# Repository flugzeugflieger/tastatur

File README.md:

for info the cherry key libraries are from https://github.com/sszczep/Cherry-MX-Breakout-Board

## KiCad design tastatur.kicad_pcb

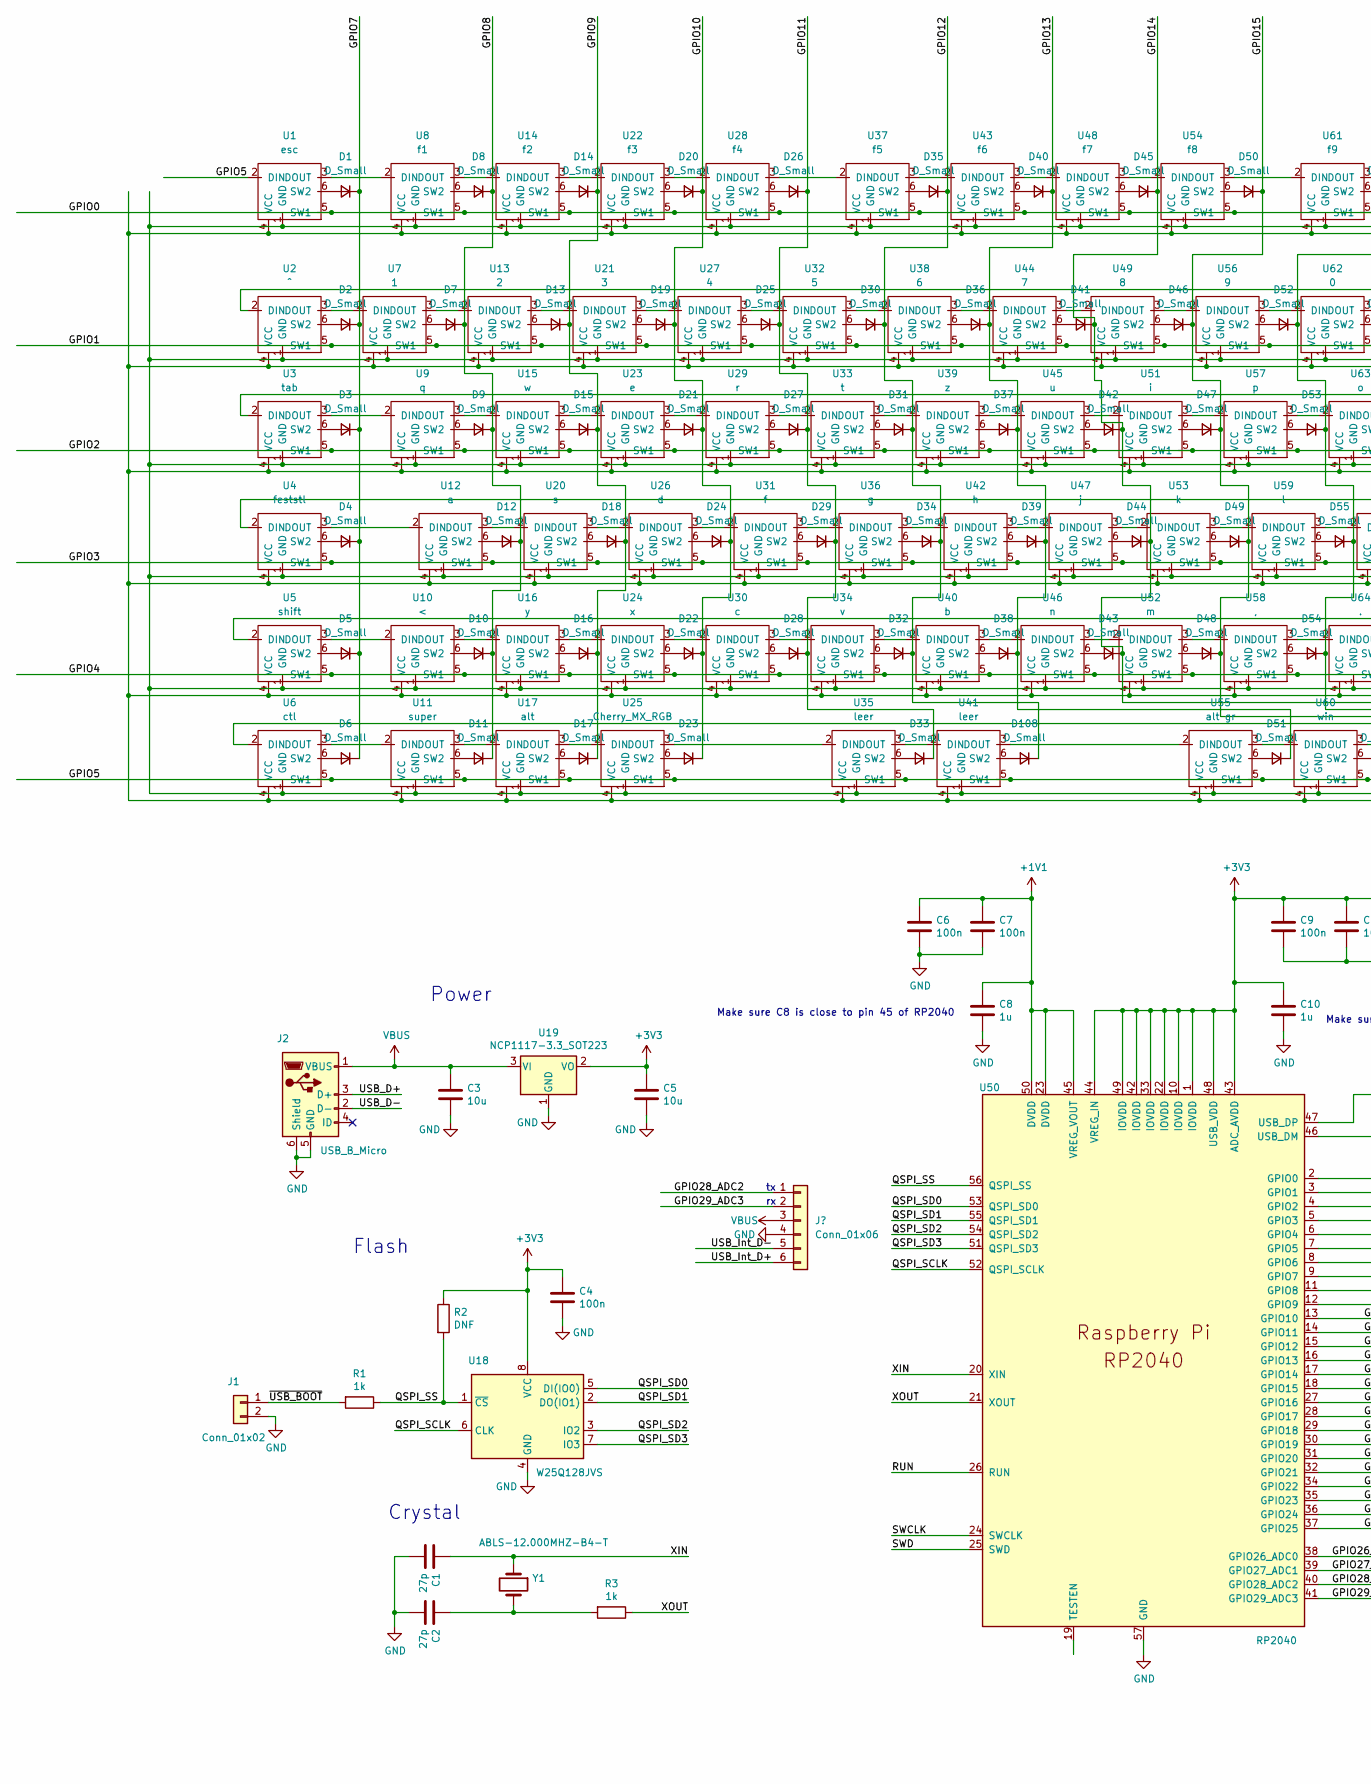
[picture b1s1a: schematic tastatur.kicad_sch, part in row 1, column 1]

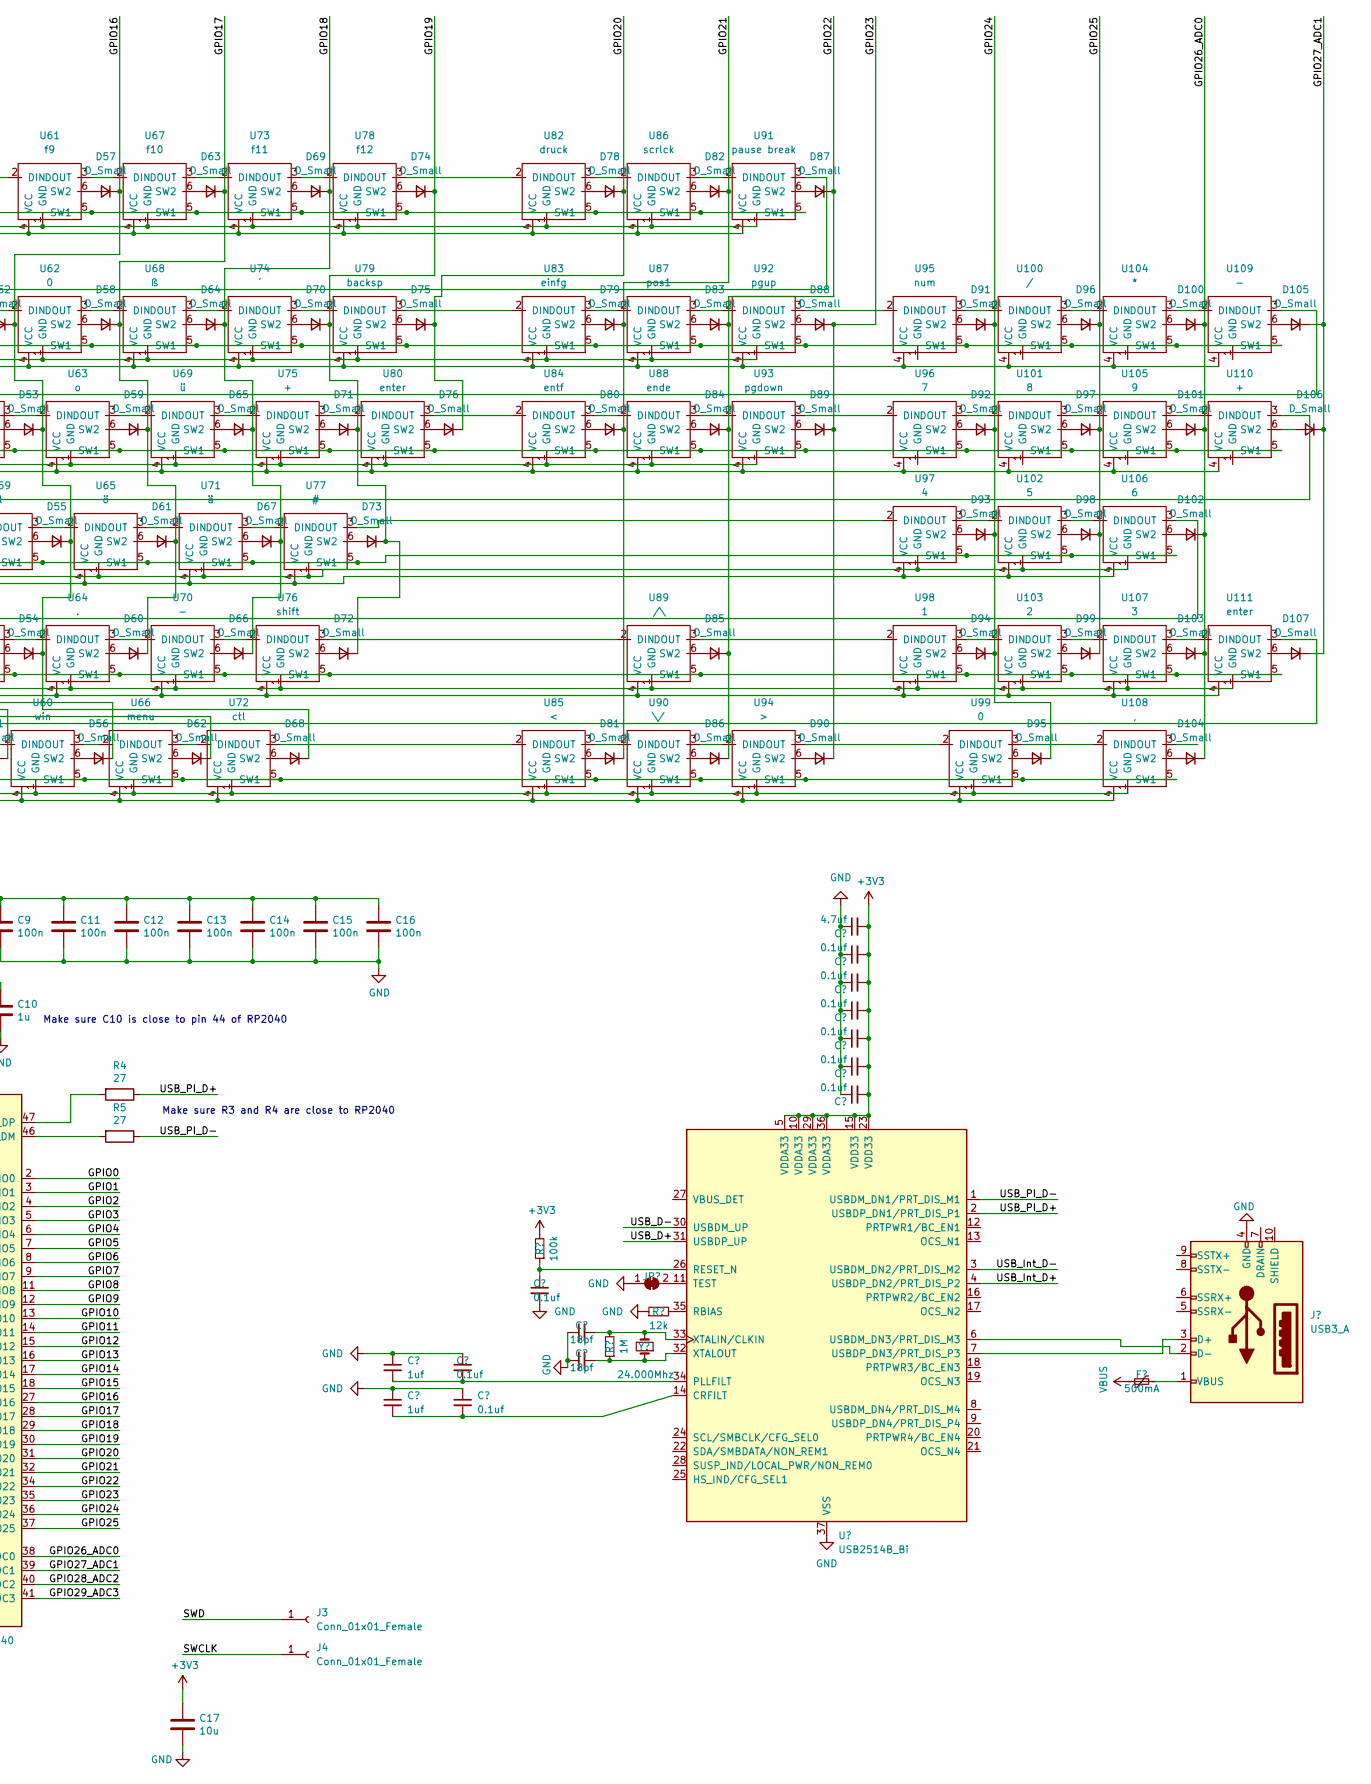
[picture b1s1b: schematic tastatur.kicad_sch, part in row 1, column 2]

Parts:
C1, C2: 27p; C_0402_1005Metric
C3, C5, C17: 10u; C_0805_2012Metric
C4, C6, C7, C9, C11, C12, C13, C14, C15, C16: 100n; C_0402_1005Metric
C8, C10: 1u; C_0402_1005Metric
D1, D2, D3, D4, D5, D6, D7, D8, D9, D10, D11, D12, D13, D14, D15, D16, D17, D18, D19, D20, D21, D22, D23, D24, D25, D26, D27, D28, D29, D30, D31, D32, D33, D34, D35, D36, D37, D38, D39, D40, D41, D42, D43, D44, D45, D46, D47, D48, D49, D50, D51, D52, D53, D54, D55, D56, D57, D58, D59, D60, D61, D62, D63, D64, D65, D66, D67, D68, D69, D70, D71, D72, D73, D74, D75, D76, D78, D79, D80, D81, D82, D83, D84, D85, D86, D87, D88, D89, D90, D91, D92, D93, D94, D95, D96, D97, D98, D99, D100, D101, D102, D103, D104, D105, D106, D107, D108: D_Small; D_SMA
J1: Conn_01x02; PinHeader_1x02_P2.54mm_Vertical
J2: USB_B_Micro; USB_Micro-B_Amphenol_10103594-0001LF_Horizontal_modified
J3: Conn_01x01_Female; LED-L1T2_LUMILEDS
J4: Conn_01x01_Female; PinSocket_1x01_P2.54mm_Vertical
R1, R3: 1k; C_0402_1005Metric
R2: DNF; C_0402_1005Metric
R4, R5: 27; C_0402_1005Metric
U1: esc; Cherry-MX_PCB-Mounted_LTST-A683CEGBW_Mill-Max-7305
U2: ^; Cherry-MX_PCB-Mounted_LTST-A683CEGBW_Mill-Max-7305
U3: tab; Cherry-MX_PCB-Mounted_LTST-A683CEGBW_Mill-Max-7305
U4: feststl; Cherry-MX_PCB-Mounted_LTST-A683CEGBW_Mill-Max-7305
U5, U76: shift; Cherry-MX_PCB-Mounted_LTST-A683CEGBW_Mill-Max-7305
U6, U72: ctl; Cherry-MX_PCB-Mounted_LTST-A683CEGBW_Mill-Max-7305
U7, U98: 1; Cherry-MX_PCB-Mounted_LTST-A683CEGBW_Mill-Max-7305
U8: f1; Cherry-MX_PCB-Mounted_LTST-A683CEGBW_Mill-Max-7305
U9: q; Cherry-MX_PCB-Mounted_LTST-A683CEGBW_Mill-Max-7305
U10, U85: <; Cherry-MX_PCB-Mounted_LTST-A683CEGBW_Mill-Max-7305
U11: super; Cherry-MX_PCB-Mounted_LTST-A683CEGBW_Mill-Max-7305
U12: a; Cherry-MX_PCB-Mounted_LTST-A683CEGBW_Mill-Max-7305
U13, U103: 2; Cherry-MX_PCB-Mounted_LTST-A683CEGBW_Mill-Max-7305
U14: f2; Cherry-MX_PCB-Mounted_LTST-A683CEGBW_Mill-Max-7305
U15: w; Cherry-MX_PCB-Mounted_LTST-A683CEGBW_Mill-Max-7305
U16: y; Cherry-MX_PCB-Mounted_LTST-A683CEGBW_Mill-Max-7305
U17: alt; Cherry-MX_PCB-Mounted_LTST-A683CEGBW_Mill-Max-7305
U18: W25Q128JVS; SOIC-8_5.23x5.23mm_P1.27mm
U19: NCP1117-3.3_SOT223; SOT-223-3_TabPin2
U20: s; Cherry-MX_PCB-Mounted_LTST-A683CEGBW_Mill-Max-7305
U21, U107: 3; Cherry-MX_PCB-Mounted_LTST-A683CEGBW_Mill-Max-7305
U22: f3; Cherry-MX_PCB-Mounted_LTST-A683CEGBW_Mill-Max-7305
U23: e; Cherry-MX_PCB-Mounted_LTST-A683CEGBW_Mill-Max-7305
U24: x; Cherry-MX_PCB-Mounted_LTST-A683CEGBW_Mill-Max-7305
U25: Cherry_MX_RGB; Cherry-MX_PCB-Mounted_LTST-A683CEGBW_Mill-Max-7305
U26: d; Cherry-MX_PCB-Mounted_LTST-A683CEGBW_Mill-Max-7305
U27, U97: 4; Cherry-MX_PCB-Mounted_LTST-A683CEGBW_Mill-Max-7305
U28: f4; Cherry-MX_PCB-Mounted_LTST-A683CEGBW_Mill-Max-7305
U29: r; Cherry-MX_PCB-Mounted_LTST-A683CEGBW_Mill-Max-7305
U30: c; Cherry-MX_PCB-Mounted_LTST-A683CEGBW_Mill-Max-7305
U31: f; Cherry-MX_PCB-Mounted_LTST-A683CEGBW_Mill-Max-7305
U32, U102: 5; Cherry-MX_PCB-Mounted_LTST-A683CEGBW_Mill-Max-7305
U33: t; Cherry-MX_PCB-Mounted_LTST-A683CEGBW_Mill-Max-7305
U34: v; Cherry-MX_PCB-Mounted_LTST-A683CEGBW_Mill-Max-7305
U35, U41: leer; Cherry-MX_PCB-Mounted_LTST-A683CEGBW_Mill-Max-7305
U36: g; Cherry-MX_PCB-Mounted_LTST-A683CEGBW_Mill-Max-7305
U37: f5; Cherry-MX_PCB-Mounted_LTST-A683CEGBW_Mill-Max-7305
U38, U106: 6; Cherry-MX_PCB-Mounted_LTST-A683CEGBW_Mill-Max-7305
U39: z; Cherry-MX_PCB-Mounted_LTST-A683CEGBW_Mill-Max-7305
U40: b; Cherry-MX_PCB-Mounted_LTST-A683CEGBW_Mill-Max-7305
U42: h; Cherry-MX_PCB-Mounted_LTST-A683CEGBW_Mill-Max-7305
U43: f6; Cherry-MX_PCB-Mounted_LTST-A683CEGBW_Mill-Max-7305
U44, U96: 7; Cherry-MX_PCB-Mounted_LTST-A683CEGBW_Mill-Max-7305
U45: u; Cherry-MX_PCB-Mounted_LTST-A683CEGBW_Mill-Max-7305
U46: n; Cherry-MX_PCB-Mounted_LTST-A683CEGBW_Mill-Max-7305
U47: j; Cherry-MX_PCB-Mounted_LTST-A683CEGBW_Mill-Max-7305
U48: f7; Cherry-MX_PCB-Mounted_LTST-A683CEGBW_Mill-Max-7305
U49, U101: 8; Cherry-MX_PCB-Mounted_LTST-A683CEGBW_Mill-Max-7305
U50: RP2040; RP2040-QFN-56
U51: i; Cherry-MX_PCB-Mounted_LTST-A683CEGBW_Mill-Max-7305
U52: m; Cherry-MX_PCB-Mounted_LTST-A683CEGBW_Mill-Max-7305
U53: k; Cherry-MX_PCB-Mounted_LTST-A683CEGBW_Mill-Max-7305
U54: f8; Cherry-MX_PCB-Mounted_LTST-A683CEGBW_Mill-Max-7305
U55: alt gr; Cherry-MX_PCB-Mounted_LTST-A683CEGBW_Mill-Max-7305
U56, U105: 9; Cherry-MX_PCB-Mounted_LTST-A683CEGBW_Mill-Max-7305
U57: p; Cherry-MX_PCB-Mounted_LTST-A683CEGBW_Mill-Max-7305
U58, U108: ,; Cherry-MX_PCB-Mounted_LTST-A683CEGBW_Mill-Max-7305
U59: l; Cherry-MX_PCB-Mounted_LTST-A683CEGBW_Mill-Max-7305
U60: win; Cherry-MX_PCB-Mounted_LTST-A683CEGBW_Mill-Max-7305
U61: f9; Cherry-MX_PCB-Mounted_LTST-A683CEGBW_Mill-Max-7305
U62, U99: 0; Cherry-MX_PCB-Mounted_LTST-A683CEGBW_Mill-Max-7305
U63: o; Cherry-MX_PCB-Mounted_LTST-A683CEGBW_Mill-Max-7305
U64: .; Cherry-MX_PCB-Mounted_LTST-A683CEGBW_Mill-Max-7305
U65: ö; Cherry-MX_PCB-Mounted_LTST-A683CEGBW_Mill-Max-7305
U66: menu; Cherry-MX_PCB-Mounted_LTST-A683CEGBW_Mill-Max-7305
U67: f10; Cherry-MX_PCB-Mounted_LTST-A683CEGBW_Mill-Max-7305
U68: ß; Cherry-MX_PCB-Mounted_LTST-A683CEGBW_Mill-Max-7305
U69: ü; Cherry-MX_PCB-Mounted_LTST-A683CEGBW_Mill-Max-7305
U70, U109: -; Cherry-MX_PCB-Mounted_LTST-A683CEGBW_Mill-Max-7305
U71: ä; Cherry-MX_PCB-Mounted_LTST-A683CEGBW_Mill-Max-7305
U73: f11; Cherry-MX_PCB-Mounted_LTST-A683CEGBW_Mill-Max-7305
U74: ´; Cherry-MX_PCB-Mounted_LTST-A683CEGBW_Mill-Max-7305
U75, U110: +; Cherry-MX_PCB-Mounted_LTST-A683CEGBW_Mill-Max-7305
U77: #; Cherry-MX_PCB-Mounted_LTST-A683CEGBW_Mill-Max-7305
U78: f12; Cherry-MX_PCB-Mounted_LTST-A683CEGBW_Mill-Max-7305
U79: backsp; Cherry-MX_PCB-Mounted_LTST-A683CEGBW_Mill-Max-7305
U80, U111: enter; Cherry-MX_PCB-Mounted_LTST-A683CEGBW_Mill-Max-7305
U82: druck; Cherry-MX_PCB-Mounted_LTST-A683CEGBW_Mill-Max-7305
U83: einfg; Cherry-MX_PCB-Mounted_LTST-A683CEGBW_Mill-Max-7305
U84: entf; Cherry-MX_PCB-Mounted_LTST-A683CEGBW_Mill-Max-7305
U86: scrlck; Cherry-MX_PCB-Mounted_LTST-A683CEGBW_Mill-Max-7305
U87: pos1; Cherry-MX_PCB-Mounted_LTST-A683CEGBW_Mill-Max-7305
U88: ende; Cherry-MX_PCB-Mounted_LTST-A683CEGBW_Mill-Max-7305
U89: /\; Cherry-MX_PCB-Mounted_LTST-A683CEGBW_Mill-Max-7305
U90: \/; Cherry-MX_PCB-Mounted_LTST-A683CEGBW_Mill-Max-7305
U91: pause break; Cherry-MX_PCB-Mounted_LTST-A683CEGBW_Mill-Max-7305
U92: pgup; Cherry-MX_PCB-Mounted_LTST-A683CEGBW_Mill-Max-7305
U93: pgdown; Cherry-MX_PCB-Mounted_LTST-A683CEGBW_Mill-Max-7305
U94: >; Cherry-MX_PCB-Mounted_LTST-A683CEGBW_Mill-Max-7305
U95: num; Cherry-MX_PCB-Mounted_LTST-A683CEGBW_Mill-Max-7305
U100: /; Cherry-MX_PCB-Mounted_LTST-A683CEGBW_Mill-Max-7305
U104: *; Cherry-MX_PCB-Mounted_LTST-A683CEGBW_Mill-Max-7305
Y1: ABLS-12.000MHZ-B4-T; Crystal_SMD_HC49-US

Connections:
+1V1: C6.1, C7.1, C8.1, U50.23 (DVDD), U50.45 (VREG_VOUT), U50.50 (DVDD)
+3V3: C4.1, C5.1, C9.1, C10.1, C11.1, C12.1, C13.1, C14.1, C15.1, C16.1, C17.1, R2.1, U18.8 (VCC), U19.2 (VO), U50.1 (IOVDD), U50.10 (IOVDD), U50.22 (IOVDD), U50.33 (IOVDD), U50.42 (IOVDD), U50.43 (ADC_AVDD), U50.44 (VREG_IN), U50.48 (USB_VDD), U50.49 (IOVDD)
/GPIO0: U1.5 (SW1), U8.5 (SW1), U14.5 (SW1), U22.5 (SW1), U28.5 (SW1), U37.5 (SW1), U43.5 (SW1), U48.5 (SW1), U50.2 (GPIO0), U54.5 (SW1), U61.5 (SW1), U67.5 (SW1), U73.5 (SW1), U78.5 (SW1), U82.5 (SW1), U86.5 (SW1), U91.5 (SW1)
/GPIO1: U2.5 (SW1), U7.5 (SW1), U13.5 (SW1), U21.5 (SW1), U27.5 (SW1), U32.5 (SW1), U38.5 (SW1), U44.5 (SW1), U49.5 (SW1), U50.3 (GPIO1), U56.5 (SW1), U62.5 (SW1), U68.5 (SW1), U74.5 (SW1), U79.5 (SW1), U83.5 (SW1), U87.5 (SW1), U92.5 (SW1), U95.5 (SW1), U100.5 (SW1), U104.5 (SW1), U109.5 (SW1)
/GPIO2: U3.5 (SW1), U9.5 (SW1), U15.5 (SW1), U23.5 (SW1), U29.5 (SW1), U33.5 (SW1), U39.5 (SW1), U45.5 (SW1), U50.4 (GPIO2), U51.5 (SW1), U57.5 (SW1), U63.5 (SW1), U69.5 (SW1), U75.5 (SW1), U80.5 (SW1), U84.5 (SW1), U88.5 (SW1), U93.5 (SW1), U96.5 (SW1), U101.5 (SW1), U105.5 (SW1), U110.5 (SW1)
/GPIO3: U4.5 (SW1), U12.5 (SW1), U20.5 (SW1), U26.5 (SW1), U31.5 (SW1), U36.5 (SW1), U42.5 (SW1), U47.5 (SW1), U50.5 (GPIO3), U53.5 (SW1), U59.5 (SW1), U65.5 (SW1), U71.5 (SW1), U77.5 (SW1), U97.5 (SW1), U102.5 (SW1), U106.5 (SW1)
/GPIO4: U5.5 (SW1), U10.5 (SW1), U16.5 (SW1), U24.5 (SW1), U30.5 (SW1), U34.5 (SW1), U40.5 (SW1), U46.5 (SW1), U50.6 (GPIO4), U52.5 (SW1), U58.5 (SW1), U64.5 (SW1), U70.5 (SW1), U76.5 (SW1), U89.5 (SW1), U98.5 (SW1), U103.5 (SW1), U107.5 (SW1), U111.5 (SW1)
/GPIO5: U1.2 (DIN), U6.5 (SW1), U11.5 (SW1), U17.5 (SW1), U25.5 (SW1), U35.5 (SW1), U41.5 (SW1), U50.7 (GPIO5), U55.5 (SW1), U60.5 (SW1), U66.5 (SW1), U72.5 (SW1), U85.5 (SW1), U90.5 (SW1), U94.5 (SW1), U99.5 (SW1), U108.5 (SW1)
/GPIO7: D1.1 (K), D2.1 (K), D3.1 (K), D4.1 (K), D5.1 (K), D6.1 (K), U50.9 (GPIO7)
/GPIO8: D7.1 (K), D8.1 (K), D9.1 (K), D10.1 (K), D11.1 (K), D12.1 (K), U50.11 (GPIO8)
/GPIO9: D13.1 (K), D14.1 (K), D15.1 (K), D16.1 (K), D17.1 (K), D18.1 (K), U50.12 (GPIO9)
/GPIO10: D19.1 (K), D20.1 (K), D21.1 (K), D22.1 (K), D23.1 (K), D24.1 (K), U50.13 (GPIO10)
/GPIO11: D25.1 (K), D26.1 (K), D27.1 (K), D28.1 (K), D29.1 (K), D33.1 (K), U50.14 (GPIO11)
/GPIO12: D30.1 (K), D31.1 (K), D32.1 (K), D34.1 (K), D35.1 (K), D108.1 (K), U50.15 (GPIO12)
/GPIO13: D36.1 (K), D37.1 (K), D38.1 (K), D39.1 (K), D40.1 (K), D51.1 (K), U50.16 (GPIO13)
/GPIO14: D41.1 (K), D42.1 (K), D43.1 (K), D44.1 (K), D45.1 (K), D56.1 (K), U50.17 (GPIO14)
/GPIO15: D46.1 (K), D47.1 (K), D48.1 (K), D49.1 (K), D50.1 (K), D62.1 (K), U50.18 (GPIO15)
/GPIO16: D52.1 (K), D53.1 (K), D54.1 (K), D55.1 (K), D57.1 (K), D68.1 (K), U50.27 (GPIO16)
/GPIO17: D58.1 (K), D59.1 (K), D60.1 (K), D61.1 (K), D63.1 (K), U50.28 (GPIO17)
/GPIO18: D64.1 (K), D65.1 (K), D66.1 (K), D67.1 (K), D69.1 (K), U50.29 (GPIO18)
/GPIO19: D70.1 (K), D71.1 (K), D72.1 (K), D73.1 (K), D74.1 (K), U50.30 (GPIO19)
/GPIO20: D75.1 (K), D76.1 (K), D78.1 (K), U50.31 (GPIO20)
/GPIO21: D79.1 (K), D80.1 (K), D81.1 (K), D82.1 (K), U50.32 (GPIO21)
/GPIO22: D83.1 (K), D84.1 (K), D85.1 (K), D86.1 (K), D87.1 (K), U50.34 (GPIO22)
/GPIO23: D88.1 (K), D89.1 (K), D90.1 (K), U50.35 (GPIO23)
/GPIO24: D91.1 (K), D92.1 (K), D93.1 (K), D94.1 (K), D95.1 (K), U50.36 (GPIO24)
/GPIO25: D96.1 (K), D97.1 (K), D98.1 (K), D99.1 (K), U50.37 (GPIO25)
/GPIO26_ADC0: D100.1 (K), D101.1 (K), D102.1 (K), D103.1 (K), D104.1 (K), U50.38 (GPIO26_ADC0)
/GPIO27_ADC1: D105.1 (K), D106.1 (K), D107.1 (K), U50.39 (GPIO27_ADC1)
/QSPI_SCLK: U18.6 (CLK), U50.52 (QSPI_SCLK)
/QSPI_SD0: U18.5 (DI(IO0)), U50.53 (QSPI_SD0)
/QSPI_SD1: U18.2 (DO(IO1)), U50.55 (QSPI_SD1)
/QSPI_SD2: U18.3 (IO2), U50.54 (QSPI_SD2)
/QSPI_SD3: U18.7 (IO3), U50.51 (QSPI_SD3)
/QSPI_SS: R1.1, R2.2, U18.1 (~CS), U50.56 (QSPI_SS)
/SWCLK: J4.1, U50.24 (SWCLK)
/SWD: J3.1, U50.25 (SWD)
/USB_D+: R4.1
/USB_D-: R5.1
/XIN: C1.1, U50.20 (XIN), Y1.1
/XOUT: R3.1, U50.21 (XOUT)
/~USB_BOOT: J1.1, R1.2
GND: C1.2, C2.2, C3.2, C4.2, C5.2, C6.2, C7.2, C8.2, C9.2, C10.2, C11.2, C12.2, C13.2, C14.2, C15.2, C16.2, C17.2, J1.2, J2.5 (GND), J2.6 (Shield), U18.4 (GND), U19.1 (GND)
unnamed: C2.1, R3.2, Y1.2
unnamed: D1.2 (A), U1.6 (SW2)
unnamed: D2.2 (A), U2.6 (SW2)
unnamed: D3.2 (A), U3.6 (SW2)
unnamed: D4.2 (A), U4.6 (SW2)
unnamed: D5.2 (A), U5.6 (SW2)
unnamed: D6.2 (A), U6.6 (SW2)
unnamed: D7.2 (A), U7.6 (SW2)
unnamed: D8.2 (A), U8.6 (SW2)
unnamed: D9.2 (A), U9.6 (SW2)
unnamed: D10.2 (A), U10.6 (SW2)
unnamed: D11.2 (A), U11.6 (SW2)
unnamed: D12.2 (A), U12.6 (SW2)
unnamed: D13.2 (A), U13.6 (SW2)
unnamed: D14.2 (A), U14.6 (SW2)
unnamed: D15.2 (A), U15.6 (SW2)
unnamed: D16.2 (A), U16.6 (SW2)
unnamed: D17.2 (A), U17.6 (SW2)
unnamed: D18.2 (A), U20.6 (SW2)
unnamed: D19.2 (A), U21.6 (SW2)
unnamed: D20.2 (A), U22.6 (SW2)
unnamed: D21.2 (A), U23.6 (SW2)
unnamed: D22.2 (A), U24.6 (SW2)
unnamed: D23.2 (A), U25.6 (SW2)
unnamed: D24.2 (A), U26.6 (SW2)
unnamed: D25.2 (A), U27.6 (SW2)
unnamed: D26.2 (A), U28.6 (SW2)
unnamed: D27.2 (A), U29.6 (SW2)
unnamed: D28.2 (A), U30.6 (SW2)
unnamed: D29.2 (A), U31.6 (SW2)
unnamed: D30.2 (A), U32.6 (SW2)
unnamed: D31.2 (A), U33.6 (SW2)
unnamed: D32.2 (A), U34.6 (SW2)
unnamed: D33.2 (A), U35.6 (SW2)
unnamed: D34.2 (A), U36.6 (SW2)
unnamed: D35.2 (A), U37.6 (SW2)
unnamed: D36.2 (A), U38.6 (SW2)
unnamed: D37.2 (A), U39.6 (SW2)
unnamed: D38.2 (A), U40.6 (SW2)
unnamed: D39.2 (A), U42.6 (SW2)
unnamed: D40.2 (A), U43.6 (SW2)
unnamed: D41.2 (A), U44.6 (SW2)
unnamed: D42.2 (A), U45.6 (SW2)
unnamed: D43.2 (A), U46.6 (SW2)
unnamed: D44.2 (A), U47.6 (SW2)
unnamed: D45.2 (A), U48.6 (SW2)
unnamed: D46.2 (A), U49.6 (SW2)
unnamed: D47.2 (A), U51.6 (SW2)
unnamed: D48.2 (A), U52.6 (SW2)
unnamed: D49.2 (A), U53.6 (SW2)
unnamed: D50.2 (A), U54.6 (SW2)
unnamed: D51.2 (A), U55.6 (SW2)
unnamed: D52.2 (A), U56.6 (SW2)
unnamed: D53.2 (A), U57.6 (SW2)
unnamed: D54.2 (A), U58.6 (SW2)
unnamed: D55.2 (A), U59.6 (SW2)
unnamed: D56.2 (A), U60.6 (SW2)
unnamed: D57.2 (A), U61.6 (SW2)
unnamed: D58.2 (A), U62.6 (SW2)
unnamed: D59.2 (A), U63.6 (SW2)
unnamed: D60.2 (A), U64.6 (SW2)
unnamed: D61.2 (A), U65.6 (SW2)
unnamed: D62.2 (A), U66.6 (SW2)
unnamed: D63.2 (A), U67.6 (SW2)
unnamed: D64.2 (A), U68.6 (SW2)
unnamed: D65.2 (A), U69.6 (SW2)
unnamed: D66.2 (A), U70.6 (SW2)
unnamed: D67.2 (A), U71.6 (SW2)
unnamed: D68.2 (A), U72.6 (SW2)
unnamed: D69.2 (A), U73.6 (SW2)
unnamed: D70.2 (A), U74.6 (SW2)
unnamed: D71.2 (A), U75.6 (SW2)
unnamed: D72.2 (A), U76.6 (SW2)
unnamed: D73.2 (A), U77.6 (SW2)
unnamed: D74.2 (A), U78.6 (SW2)
unnamed: D75.2 (A), U79.6 (SW2)
unnamed: D76.2 (A), U80.6 (SW2)
unnamed: D78.2 (A), U82.6 (SW2)
unnamed: D79.2 (A), U83.6 (SW2)
unnamed: D80.2 (A), U84.6 (SW2)
unnamed: D81.2 (A), U85.6 (SW2)
unnamed: D82.2 (A), U86.6 (SW2)
unnamed: D83.2 (A), U87.6 (SW2)
unnamed: D84.2 (A), U88.6 (SW2)
unnamed: D85.2 (A), U89.6 (SW2)
unnamed: D86.2 (A), U90.6 (SW2)
unnamed: D87.2 (A), U91.6 (SW2)
unnamed: D88.2 (A), U92.6 (SW2)
unnamed: D89.2 (A), U93.6 (SW2)
unnamed: D90.2 (A), U94.6 (SW2)
unnamed: D91.2 (A), U95.6 (SW2)
unnamed: D92.2 (A), U96.6 (SW2)
unnamed: D93.2 (A), U97.6 (SW2)
unnamed: D94.2 (A), U98.6 (SW2)
unnamed: D95.2 (A), U99.6 (SW2)
unnamed: D96.2 (A), U100.6 (SW2)
unnamed: D97.2 (A), U101.6 (SW2)
unnamed: D98.2 (A), U102.6 (SW2)
unnamed: D99.2 (A), U103.6 (SW2)
unnamed: D100.2 (A), U104.6 (SW2)
unnamed: D101.2 (A), U105.6 (SW2)
unnamed: D102.2 (A), U106.6 (SW2)
unnamed: D103.2 (A), U107.6 (SW2)
unnamed: D104.2 (A), U108.6 (SW2)
unnamed: D105.2 (A), U109.6 (SW2)
unnamed: D106.2 (A), U110.6 (SW2)
unnamed: D107.2 (A), U111.6 (SW2)
unnamed: R4.2, U50.47 (USB_DP)
unnamed: R5.2, U50.46 (USB_DM)
unnamed: U1.1 (GND), U2.1 (GND), U3.1 (GND), U4.1 (GND), U5.1 (GND), U6.1 (GND), U7.1 (GND), U8.1 (GND), U9.1 (GND), U10.1 (GND), U11.1 (GND), U12.1 (GND), U13.1 (GND), U14.1 (GND), U15.1 (GND), U16.1 (GND), U17.1 (GND), U20.1 (GND), U21.1 (GND), U22.1 (GND), U23.1 (GND), U24.1 (GND), U25.1 (GND), U26.1 (GND), U27.1 (GND), U28.1 (GND), U29.1 (GND), U30.1 (GND), U31.1 (GND), U32.1 (GND), U33.1 (GND), U34.1 (GND), U35.1 (GND), U36.1 (GND), U37.1 (GND), U38.1 (GND), U39.1 (GND), U40.1 (GND), U41.1 (GND), U42.1 (GND), U43.1 (GND), U44.1 (GND), U45.1 (GND), U46.1 (GND), U47.1 (GND), U48.1 (GND), U49.1 (GND), U51.1 (GND), U52.1 (GND), U53.1 (GND), U54.1 (GND), U55.1 (GND), U56.1 (GND), U57.1 (GND), U58.1 (GND), U59.1 (GND), U60.1 (GND), U61.1 (GND), U62.1 (GND), U63.1 (GND), U64.1 (GND), U65.1 (GND), U66.1 (GND), U67.1 (GND), U68.1 (GND), U69.1 (GND), U70.1 (GND), U71.1 (GND), U72.1 (GND), U73.1 (GND), U74.1 (GND), U75.1 (GND), U76.1 (GND), U77.1 (GND), U78.1 (GND), U79.1 (GND), U80.1 (GND), U82.1 (GND), U83.1 (GND), U84.1 (GND), U85.1 (GND), U86.1 (GND), U87.1 (GND), U88.1 (GND), U89.1 (GND), U90.1 (GND), U91.1 (GND), U92.1 (GND), U93.1 (GND), U94.1 (GND), U97.1 (GND), U98.1 (GND), U99.1 (GND), U102.1 (GND), U103.1 (GND), U106.1 (GND), U107.1 (GND), U108.1 (GND), U111.1 (GND)
unnamed: U1.3 (DOUT), U8.2 (DIN)
unnamed: U1.4 (VCC), U2.4 (VCC), U3.4 (VCC), U4.4 (VCC), U5.4 (VCC), U6.4 (VCC), U7.4 (VCC), U8.4 (VCC), U9.4 (VCC), U10.4 (VCC), U11.4 (VCC), U12.4 (VCC), U13.4 (VCC), U14.4 (VCC), U15.4 (VCC), U16.4 (VCC), U17.4 (VCC), U20.4 (VCC), U21.4 (VCC), U22.4 (VCC), U23.4 (VCC), U24.4 (VCC), U25.4 (VCC), U26.4 (VCC), U27.4 (VCC), U28.4 (VCC), U29.4 (VCC), U30.4 (VCC), U31.4 (VCC), U32.4 (VCC), U33.4 (VCC), U34.4 (VCC), U35.4 (VCC), U36.4 (VCC), U37.4 (VCC), U38.4 (VCC), U39.4 (VCC), U40.4 (VCC), U41.4 (VCC), U42.4 (VCC), U43.4 (VCC), U44.4 (VCC), U45.4 (VCC), U46.4 (VCC), U47.4 (VCC), U48.4 (VCC), U49.4 (VCC), U51.4 (VCC), U52.4 (VCC), U53.4 (VCC), U54.4 (VCC), U55.4 (VCC), U56.4 (VCC), U57.4 (VCC), U58.4 (VCC), U59.4 (VCC), U60.4 (VCC), U61.4 (VCC), U62.4 (VCC), U63.4 (VCC), U64.4 (VCC), U65.4 (VCC), U66.4 (VCC), U67.4 (VCC), U68.4 (VCC), U69.4 (VCC), U70.4 (VCC), U71.4 (VCC), U72.4 (VCC), U73.4 (VCC), U74.4 (VCC), U75.4 (VCC), U76.4 (VCC), U77.4 (VCC), U78.4 (VCC), U79.4 (VCC), U80.4 (VCC), U82.4 (VCC), U83.4 (VCC), U84.4 (VCC), U85.4 (VCC), U86.4 (VCC), U87.4 (VCC), U88.4 (VCC), U89.4 (VCC), U90.4 (VCC), U91.4 (VCC), U92.4 (VCC), U93.4 (VCC), U94.4 (VCC), U95.4 (VCC), U96.4 (VCC), U97.4 (VCC), U98.4 (VCC), U99.4 (VCC), U100.4 (VCC), U101.4 (VCC), U102.4 (VCC), U103.4 (VCC), U104.4 (VCC), U105.4 (VCC), U106.4 (VCC), U107.4 (VCC), U108.4 (VCC), U109.4 (VCC), U110.4 (VCC), U111.4 (VCC)
unnamed: U2.2 (DIN), U91.3 (DOUT)
unnamed: U2.3 (DOUT), U7.2 (DIN)
unnamed: U3.3 (DOUT), U9.2 (DIN)
unnamed: U5.3 (DOUT), U10.2 (DIN)
unnamed: U10.3 (DOUT), U16.2 (DIN)
unnamed: U6.3 (DOUT), U11.2 (DIN)
unnamed: U11.3 (DOUT), U17.2 (DIN)
unnamed: U4.3 (DOUT), U12.2 (DIN)
unnamed: U12.3 (DOUT), U20.2 (DIN)
unnamed: U7.3 (DOUT), U13.2 (DIN)
unnamed: U13.3 (DOUT), U21.2 (DIN)
unnamed: U8.3 (DOUT), U14.2 (DIN)
unnamed: U14.3 (DOUT), U22.2 (DIN)
unnamed: U9.3 (DOUT), U15.2 (DIN)
unnamed: U15.3 (DOUT), U23.2 (DIN)
unnamed: U16.3 (DOUT), U24.2 (DIN)
unnamed: U17.3 (DOUT), U25.2 (DIN)
unnamed: U20.3 (DOUT), U26.2 (DIN)
unnamed: U21.3 (DOUT), U27.2 (DIN)
unnamed: U22.3 (DOUT), U28.2 (DIN)
unnamed: U23.3 (DOUT), U29.2 (DIN)
unnamed: U24.3 (DOUT), U30.2 (DIN)
unnamed: U25.3 (DOUT), U35.2 (DIN)
unnamed: U26.3 (DOUT), U31.2 (DIN)
unnamed: U27.3 (DOUT), U32.2 (DIN)
unnamed: U28.3 (DOUT), U37.2 (DIN)
unnamed: U29.3 (DOUT), U33.2 (DIN)
unnamed: U30.3 (DOUT), U34.2 (DIN)
unnamed: U31.3 (DOUT), U36.2 (DIN)
unnamed: U32.3 (DOUT), U38.2 (DIN)
unnamed: U33.3 (DOUT), U39.2 (DIN)
unnamed: U34.3 (DOUT), U40.2 (DIN)
unnamed: U35.3 (DOUT), U41.2 (DIN)
unnamed: U36.3 (DOUT), U42.2 (DIN)
unnamed: U37.3 (DOUT), U43.2 (DIN)
unnamed: U38.3 (DOUT), U44.2 (DIN)
unnamed: U39.3 (DOUT), U45.2 (DIN)
unnamed: U40.3 (DOUT), U46.2 (DIN)
unnamed: U41.3 (DOUT), U55.2 (DIN)
unnamed: D108.2 (A), U41.6 (SW2)
unnamed: U42.3 (DOUT), U47.2 (DIN)
unnamed: U43.3 (DOUT), U48.2 (DIN)
unnamed: U44.3 (DOUT), U49.2 (DIN)
unnamed: U45.3 (DOUT), U51.2 (DIN)
unnamed: U46.3 (DOUT), U52.2 (DIN)
unnamed: U47.3 (DOUT), U53.2 (DIN)
unnamed: U48.3 (DOUT), U54.2 (DIN)
unnamed: U49.3 (DOUT), U56.2 (DIN)
unnamed: U51.3 (DOUT), U57.2 (DIN)
unnamed: U52.3 (DOUT), U58.2 (DIN)
unnamed: U53.3 (DOUT), U59.2 (DIN)
unnamed: U54.3 (DOUT), U61.2 (DIN)
unnamed: U55.3 (DOUT), U60.2 (DIN)
unnamed: U56.3 (DOUT), U62.2 (DIN)
unnamed: U57.3 (DOUT), U63.2 (DIN)
unnamed: U58.3 (DOUT), U64.2 (DIN)
unnamed: U59.3 (DOUT), U65.2 (DIN)
unnamed: U60.3 (DOUT), U66.2 (DIN)
unnamed: U61.3 (DOUT), U67.2 (DIN)
unnamed: U62.3 (DOUT), U68.2 (DIN)
unnamed: U63.3 (DOUT), U69.2 (DIN)
unnamed: U64.3 (DOUT), U70.2 (DIN)
unnamed: U65.3 (DOUT), U71.2 (DIN)
unnamed: U66.3 (DOUT), U72.2 (DIN)
unnamed: U67.3 (DOUT), U73.2 (DIN)
unnamed: U68.3 (DOUT), U74.2 (DIN)
unnamed: U69.3 (DOUT), U75.2 (DIN)
unnamed: U70.3 (DOUT), U76.2 (DIN)
unnamed: U71.3 (DOUT), U77.2 (DIN)
unnamed: U72.3 (DOUT), U85.2 (DIN)
unnamed: U73.3 (DOUT), U78.2 (DIN)
unnamed: U74.3 (DOUT), U79.2 (DIN)
unnamed: U75.3 (DOUT), U80.2 (DIN)
unnamed: U76.3 (DOUT), U89.2 (DIN)
unnamed: U77.3 (DOUT), U97.2 (DIN)
unnamed: U78.3 (DOUT), U82.2 (DIN)
unnamed: U79.3 (DOUT), U83.2 (DIN)
unnamed: U80.3 (DOUT), U84.2 (DIN)
unnamed: U82.3 (DOUT), U86.2 (DIN)
unnamed: U83.3 (DOUT), U87.2 (DIN)
unnamed: U84.3 (DOUT), U88.2 (DIN)
unnamed: U85.3 (DOUT), U90.2 (DIN)
unnamed: U86.3 (DOUT), U91.2 (DIN)
unnamed: U87.3 (DOUT), U92.2 (DIN)
unnamed: U88.3 (DOUT), U93.2 (DIN)
unnamed: U89.3 (DOUT), U98.2 (DIN)
unnamed: U90.3 (DOUT), U94.2 (DIN)
unnamed: U92.3 (DOUT), U95.2 (DIN)
unnamed: U93.3 (DOUT), U96.2 (DIN)
unnamed: U94.3 (DOUT), U99.2 (DIN)
unnamed: U95.3 (DOUT), U100.2 (DIN)
unnamed: U100.3 (DOUT), U104.2 (DIN)
unnamed: U96.3 (DOUT), U101.2 (DIN)
unnamed: U101.3 (DOUT), U105.2 (DIN)
unnamed: U97.3 (DOUT), U102.2 (DIN)
unnamed: U102.3 (DOUT), U106.2 (DIN)
unnamed: U98.3 (DOUT), U103.2 (DIN)
unnamed: U103.3 (DOUT), U107.2 (DIN)
unnamed: U104.3 (DOUT), U109.2 (DIN)
unnamed: U105.3 (DOUT), U110.2 (DIN)
unnamed: U5.2 (DIN), U106.3 (DOUT)
unnamed: U107.3 (DOUT), U111.2 (DIN)
unnamed: U99.3 (DOUT), U108.2 (DIN)
unnamed: U3.2 (DIN), U109.3 (DOUT)
unnamed: U4.2 (DIN), U110.3 (DOUT)
unnamed: U6.2 (DIN), U111.3 (DOUT)
VBUS: C3.1, J2.1 (VBUS), U19.3 (VI)

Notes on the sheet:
Make sure C10 is close to pin 44 of RP2040
Flash
Crystal
Make sure R3 and R4 are close to RP2040
Power
Make sure C8 is close to pin 45 of RP2040

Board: 2 copper layers, 241 parts (106 on the bottom side), 249 nets, no tracks yet.

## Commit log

2023-03-18 init-ish
2023-03-18 keine backups gebraucht!
2023-03-18 https://github.com/sszczep/Cherry-MX-Breakout-Board
